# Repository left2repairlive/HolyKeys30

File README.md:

## Concept
I wanted a one-handed keyboard for gaming on the go, but the offerings on the market seemed cheap, quiet pricy and way to RGB and aggressive looking.
I decided to give it a try and started a wish-list:

1. wired (for now)
2. no RGB
3. no extras like a screen or knobs (for now)
4. no layering (broke that rule)

After getting started I decided to design the PCB 100% reversible, so I could populate it from either side and use the same PCB for a right or left hand keyboard if I ever wanted to extend this project to an actual typing keyboard.

## Layout
I used Keyboard Layout Editor and came up with [this design](https://keyboard-layout-editor.com/##@@_c=%23cc0000&a:7%3B&=Esc&_c=%23cccccc%3B&=1&=2&=3&=4&=5&_x:1.25%3B&=6&=7&=8&=9&=0&=%E2%86%90%3B&@=Tab&=Q&_c=%23444444&t=%23Cccccc&n:true%3B&=W&_c=%23cccccc&t=%23000000%3B&=E&=R&=T&_x:1.25%3B&=Y&=U&_c=%23444444&t=%23cccccc&n:true%3B&=I&_c=%23cccccc&t=%23000000%3B&=O&=P&=Del%3B&@=Caps&_c=%23444444&t=%23CCCCCC%3B&=A&_t=%23Cccccc%3B&=S&=D&_c=%23cccccc&t=%23000000%3B&=F&=G&_x:1.25%3B&=H&_c=%23444444&t=%23cccccc%3B&=J&=K&=L&_c=%23cccccc&t=%23000000%3B&='&=Enter%3B&@=Shift&=Z&=X&=C&=V&=B&_x:1.25%3B&=N&=M&=,&=.&=%2F%2F&=Shift%3B&@=Ctrl&=Win&=Alt&_w:3%3B&=&_x:1.25&w:3%3B&=&=Alt&=Ctrl&=Fn) for both sides.
The 3u spacebar will still have all three units populated with hot swap sockets in case I want to actually use all 30 keys of the 6x5 grid.

## Switches
I defininetily wanted low-profile switches, finally deciding on Kalih Choc V2. I ordered a bunch of different switches to test out, but after playing around I landed on basic linear Reds. I will give tactile switches a try in the future.

## MCU-Selection
The Arduino Pro Micro seemed like the easiest and most popular choice, but I also ordered some others to play around with. The nRF-series seems very promosing in the future.
I designed the PCB to only have pin-sockets for the actual rows and columns I need, so I won't settle for on specific MCU right away, but can swap them out easily.

## Firmware
For the sake of fun I decided to write the firmware myself as a challenge for learning some more micro-controller programming.

## KiCAD libraries
* [kiswitch library](https://github.com/kiswitch/kiswitch)
* [ScottoKeebs library](https://github.com/joe-scotto/scottokeebs/tree/main/Extras/ScottoKicad)

*As said above I may have misused the relative paths for these libraries, so it needs fixing*

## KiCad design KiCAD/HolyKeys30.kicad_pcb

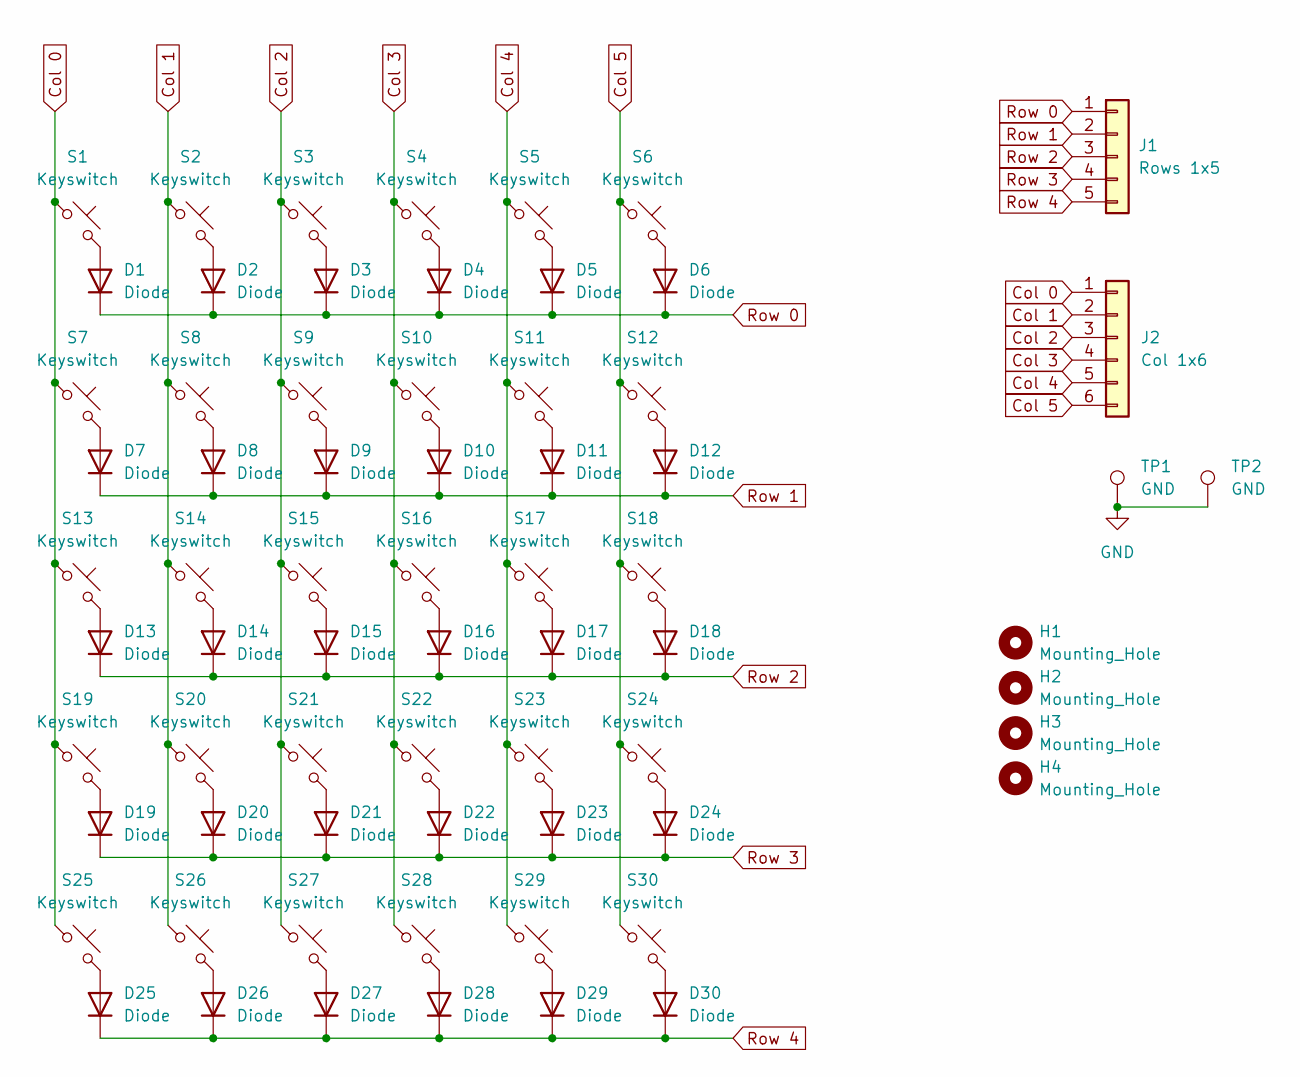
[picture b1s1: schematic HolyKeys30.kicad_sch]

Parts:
D1, D2, D3, D4, D5, D6, D7, D8, D9, D10, D11, D12, D13, D14, D15, D16, D17, D18, D19, D20, D21, D22, D23, D24, D25, D26, D27, D28, D29, D30: Diode; Diode_DO-35
H1, H2, H3, H4: Mounting_Hole; MountingHole_2.2mm_M2_DIN965
J1: Rows 1x5; PinSocket_1x05_P2.54mm_Vertical
J2: Col 1x6; PinSocket_1x06_P2.54mm_Vertical
S1, S2, S3, S4, S5, S6, S7, S8, S9, S10, S11, S12, S13, S14, S15, S16, S17, S18, S19, S20, S21, S22, S23, S24, S25, S26, S27, S28, S29, S30: Keyswitch; SW_Hotswap_Kailh_Choc_V1V2_Reversible
TP1, TP2: GND; TestPoint_Pad_D2.5mm

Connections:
Col 0: J2.1, S1.1, S7.1, S13.1, S19.1, S25.1
Col 1: J2.2, S2.1, S8.1, S14.1, S20.1, S26.1
Col 2: J2.3, S3.1, S9.1, S15.1, S21.1, S27.1
Col 3: J2.4, S4.1, S10.1, S16.1, S22.1, S28.1
Col 4: J2.5, S5.1, S11.1, S17.1, S23.1, S29.1
Col 5: J2.6, S6.1, S12.1, S18.1, S24.1, S30.1
GND: TP1.1, TP2.1
unnamed: D1.2 (A), S1.2
unnamed: D2.2 (A), S2.2
unnamed: D3.2 (A), S3.2
unnamed: D4.2 (A), S4.2
unnamed: D5.2 (A), S5.2
unnamed: D6.2 (A), S6.2
unnamed: D7.2 (A), S7.2
unnamed: D8.2 (A), S8.2
unnamed: D9.2 (A), S9.2
unnamed: D10.2 (A), S10.2
unnamed: D11.2 (A), S11.2
unnamed: D12.2 (A), S12.2
unnamed: D13.2 (A), S13.2
unnamed: D14.2 (A), S14.2
unnamed: D15.2 (A), S15.2
unnamed: D16.2 (A), S16.2
unnamed: D17.2 (A), S17.2
unnamed: D18.2 (A), S18.2
unnamed: D19.2 (A), S19.2
unnamed: D20.2 (A), S20.2
unnamed: D21.2 (A), S21.2
unnamed: D22.2 (A), S22.2
unnamed: D23.2 (A), S23.2
unnamed: D24.2 (A), S24.2
unnamed: D25.2 (A), S25.2
unnamed: D26.2 (A), S26.2
unnamed: D27.2 (A), S27.2
unnamed: D28.2 (A), S28.2
unnamed: D29.2 (A), S29.2
unnamed: D30.2 (A), S30.2
Row 0: D1.1 (K), D2.1 (K), D3.1 (K), D4.1 (K), D5.1 (K), D6.1 (K), J1.1
Row 1: D7.1 (K), D8.1 (K), D9.1 (K), D10.1 (K), D11.1 (K), D12.1 (K), J1.2
Row 2: D13.1 (K), D14.1 (K), D15.1 (K), D16.1 (K), D17.1 (K), D18.1 (K), J1.3
Row 3: D19.1 (K), D20.1 (K), D21.1 (K), D22.1 (K), D23.1 (K), D24.1 (K), J1.4
Row 4: D25.1 (K), D26.1 (K), D27.1 (K), D28.1 (K), D29.1 (K), D30.1 (K), J1.5

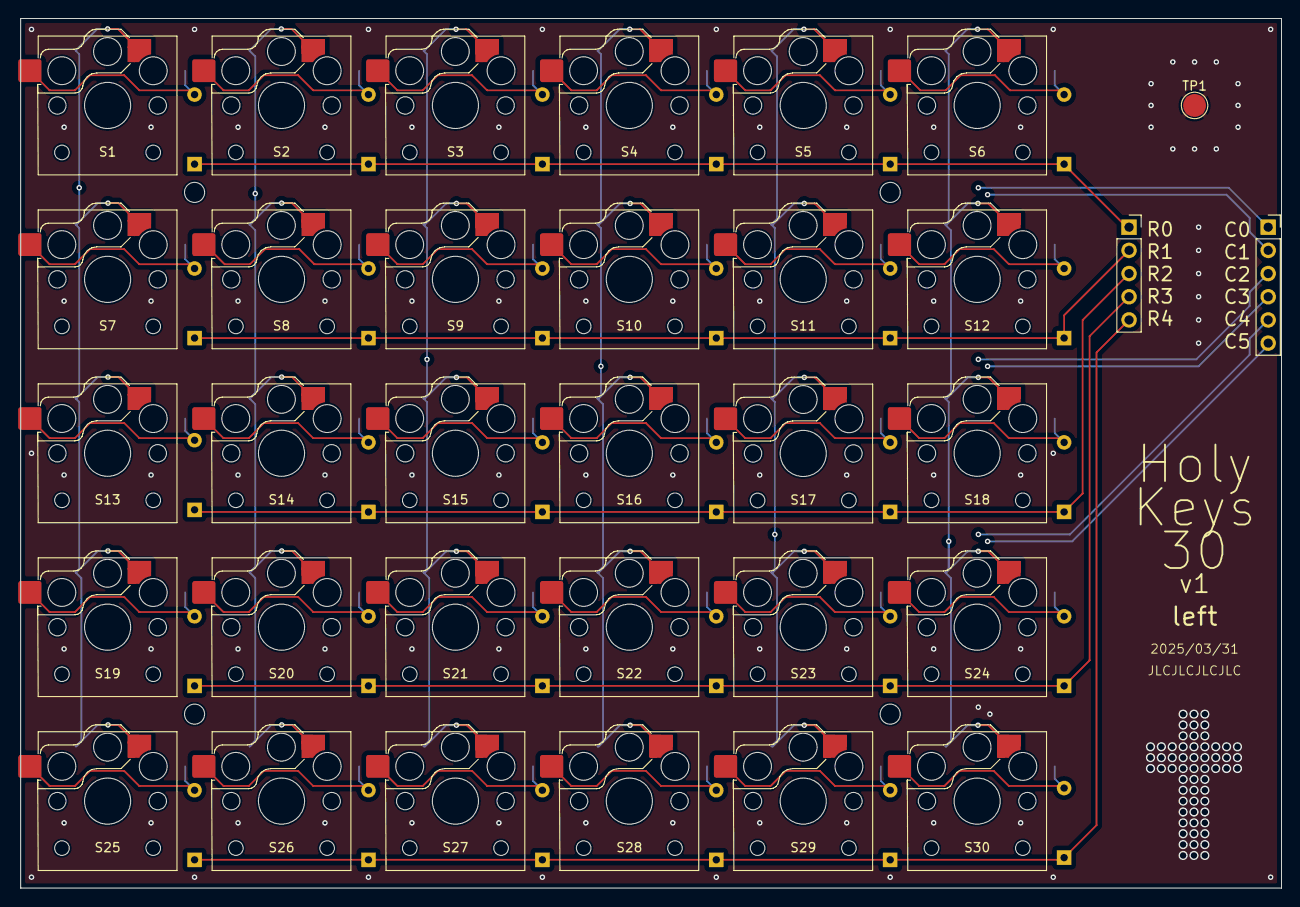
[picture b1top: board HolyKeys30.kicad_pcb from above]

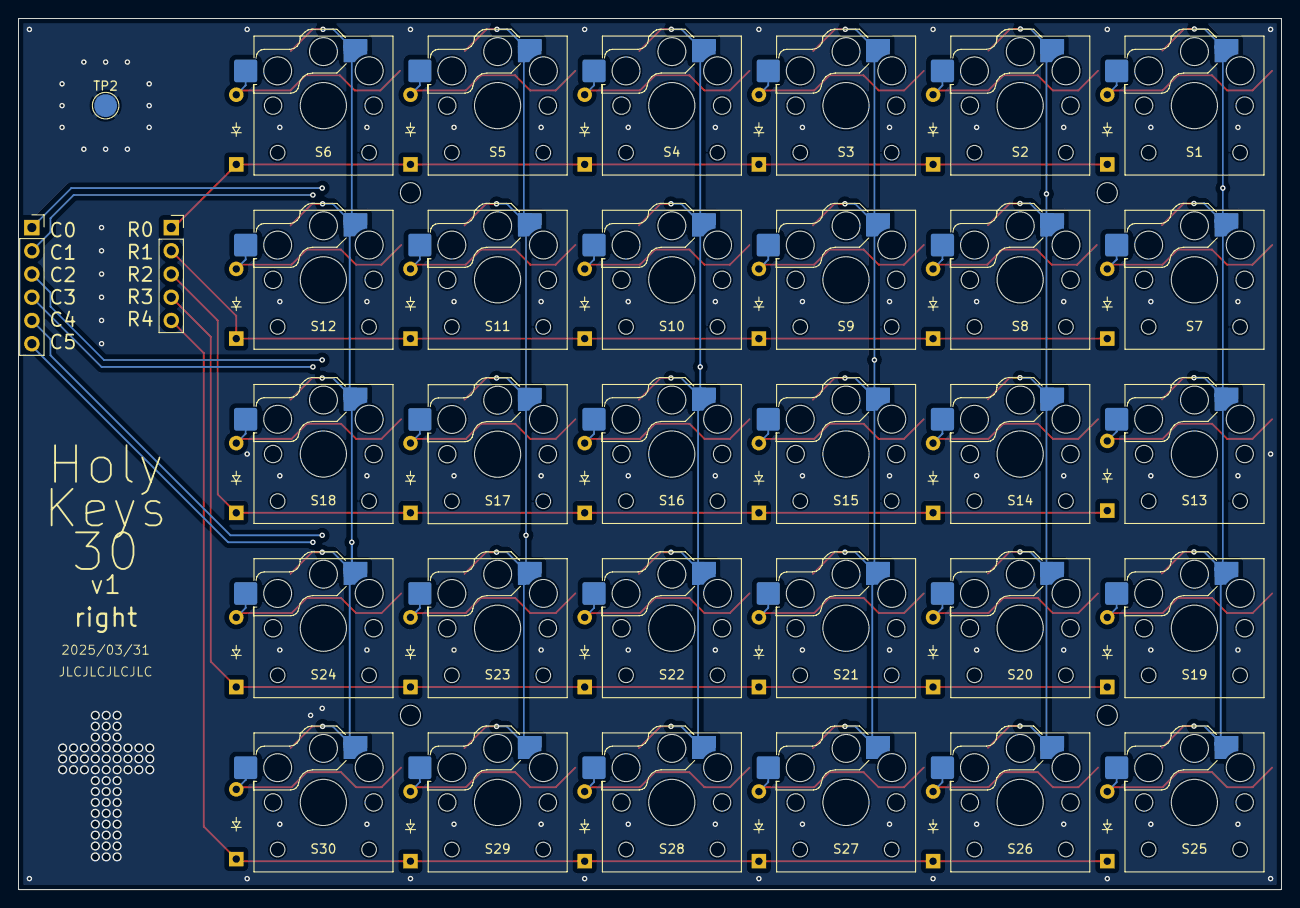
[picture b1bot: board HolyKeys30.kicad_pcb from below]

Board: 4 copper layers, 138.1 x 95.2 mm, 68 parts (31 on the bottom side), 42 nets.

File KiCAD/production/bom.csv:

Designator,Footprint,Quantity,Value,LCSC Part #
"D1, D10, D11, D12, D13, D14, D15, D16, D17, D18, D19, D2, D20, D21, D22, D23, D24, D25, D26, D27, D28, D29, D3, D30, D4, D5, D6, D7, D8, D9",Diode_DO-35,30,Diode,
"H1, H2, H3, H4",MountingHole_2.2mm_M2_DIN965,4,Mounting_Hole,
J1,PinSocket_1x05_P2.54mm_Vertical,1,Rows 1x5,
J2,PinSocket_1x06_P2.54mm_Vertical,1,Col 1x6,
"S1, S10, S11, S12, S13, S14, S15, S16, S17, S18, S19, S2, S20, S21, S22, S23, S24, S25, S26, S27, S28, S29, S3, S30, S4, S5, S6, S7, S8, S9",SW_Hotswap_Kailh_Choc_V1V2_Reversible,30,Keyswitch,
"TP1, TP2",TestPoint_Pad_D2.5mm,2,GND,

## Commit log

2025-04-02 Added disclaimer for non-linked library paths
2025-04-02 Designed parametric keycap and renamed files
2025-04-02 Updated plate to incorporate stabilizers
2025-04-15 Adjusted custom keycaps for better sizing and fit
2025-04-15 Added angle variable and choc v2 stabilizers
2025-04-15 Minor tweaks to dimensions
2025-04-17 Started refactoring 3D design to make it more modular
